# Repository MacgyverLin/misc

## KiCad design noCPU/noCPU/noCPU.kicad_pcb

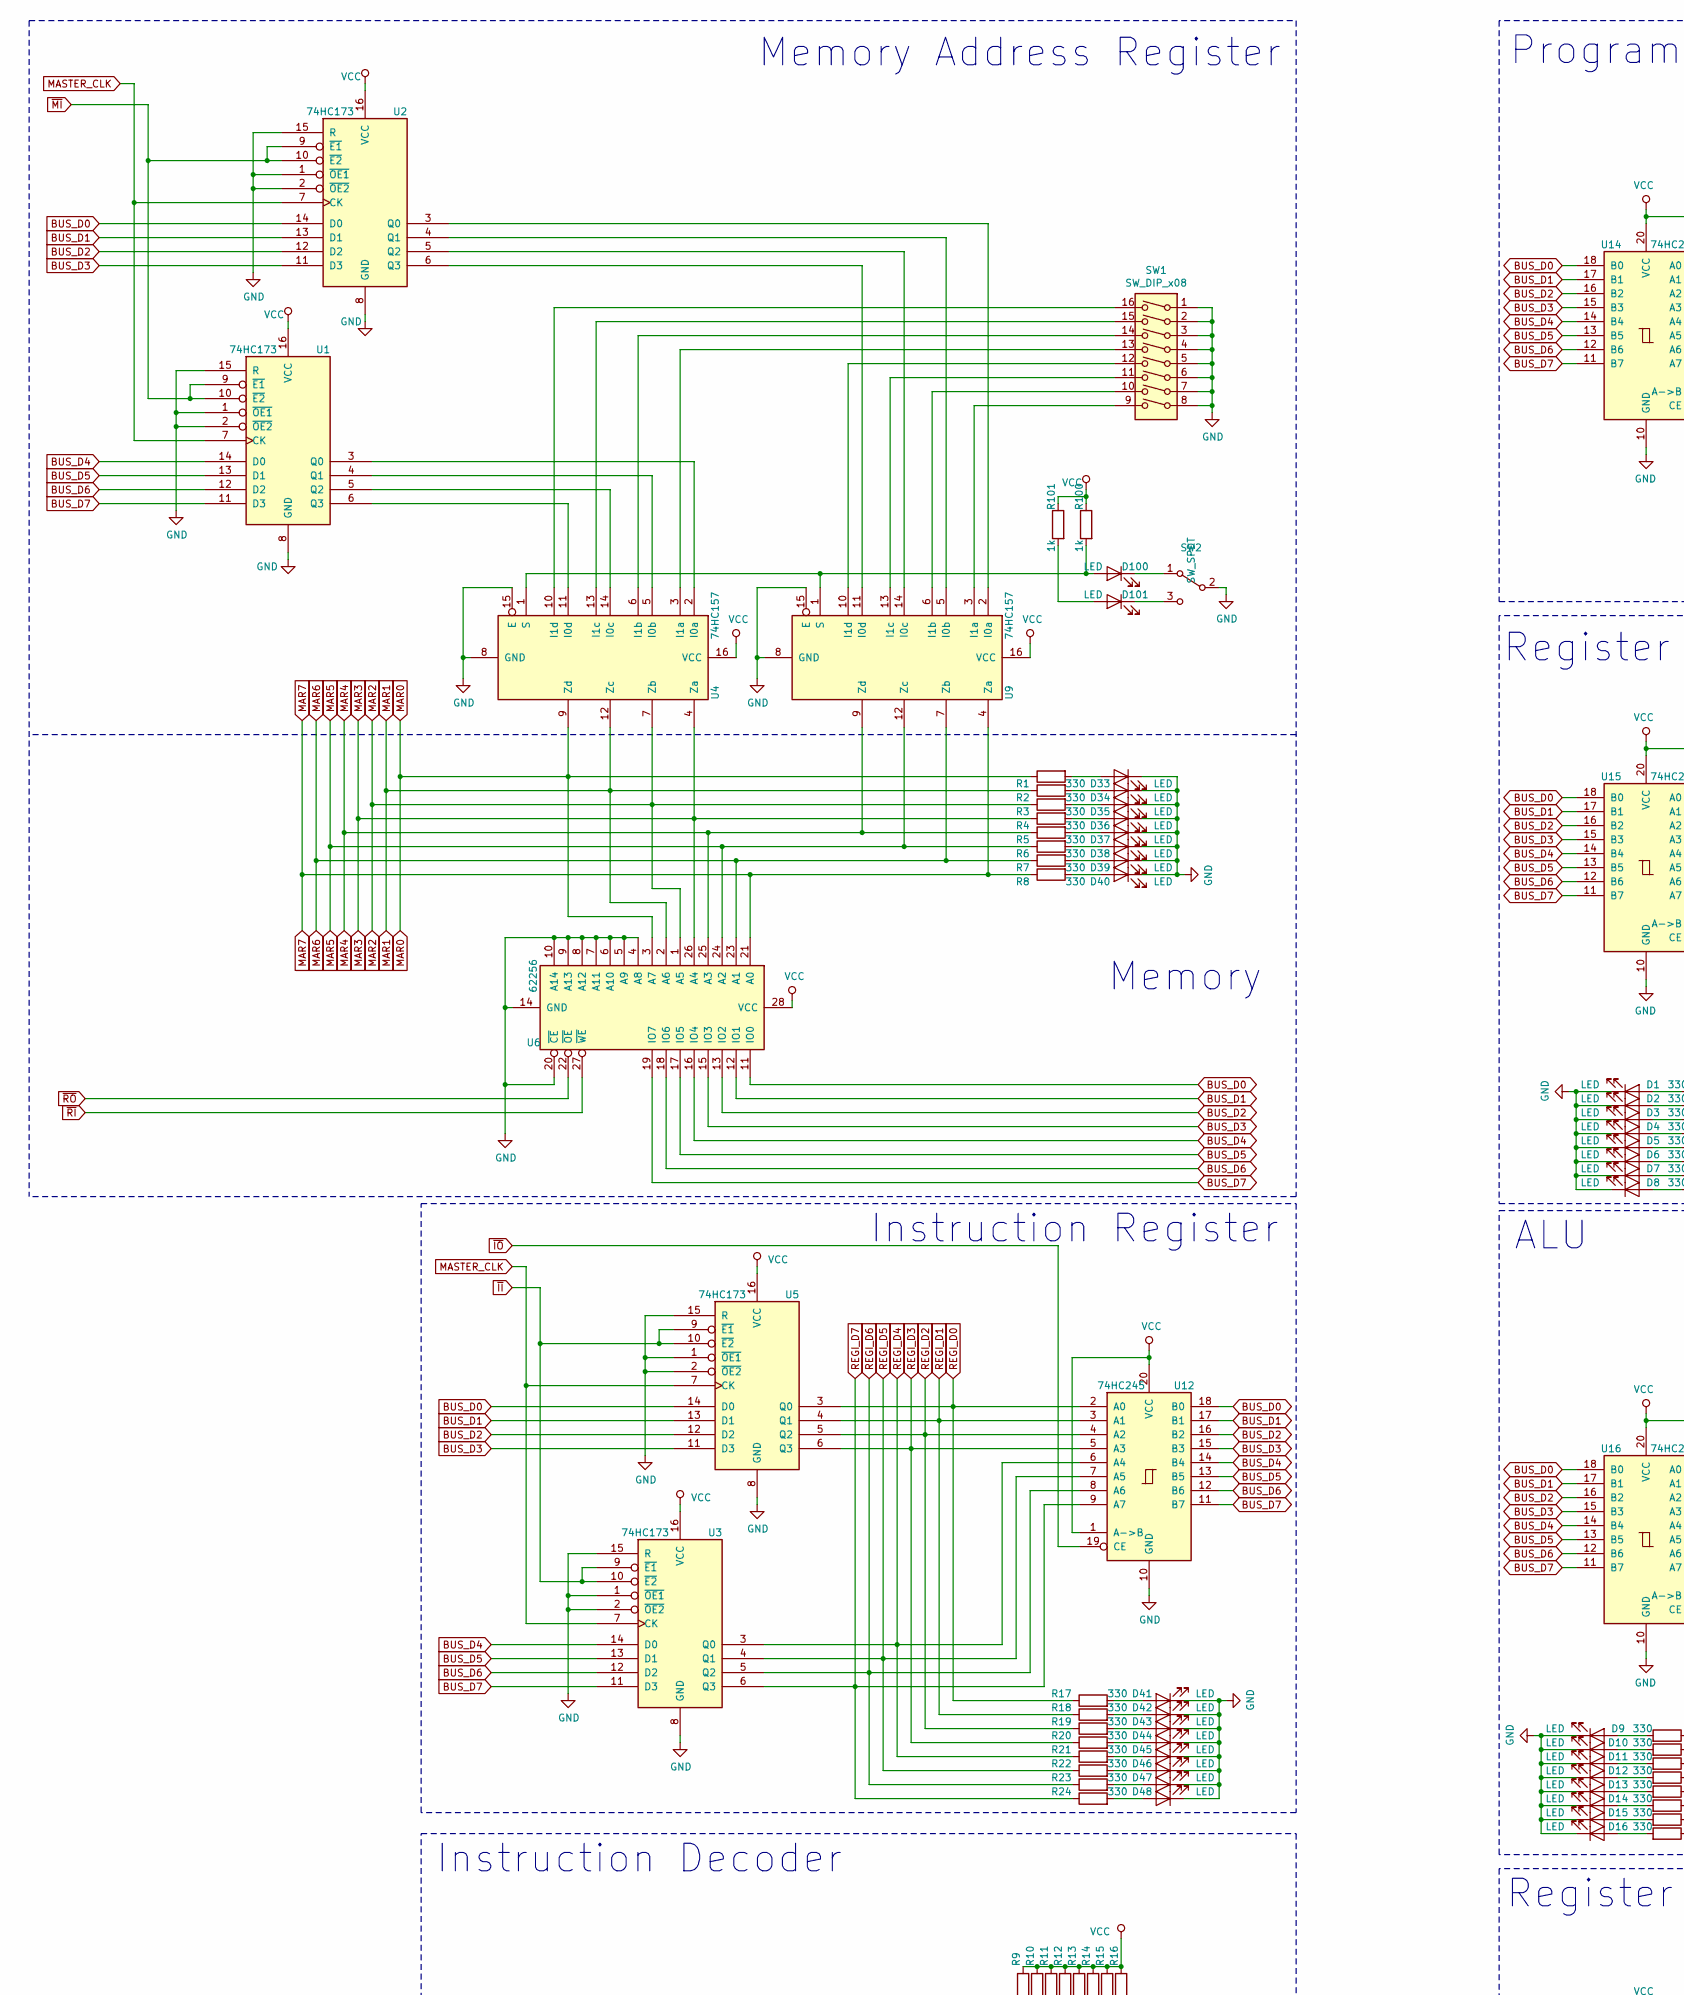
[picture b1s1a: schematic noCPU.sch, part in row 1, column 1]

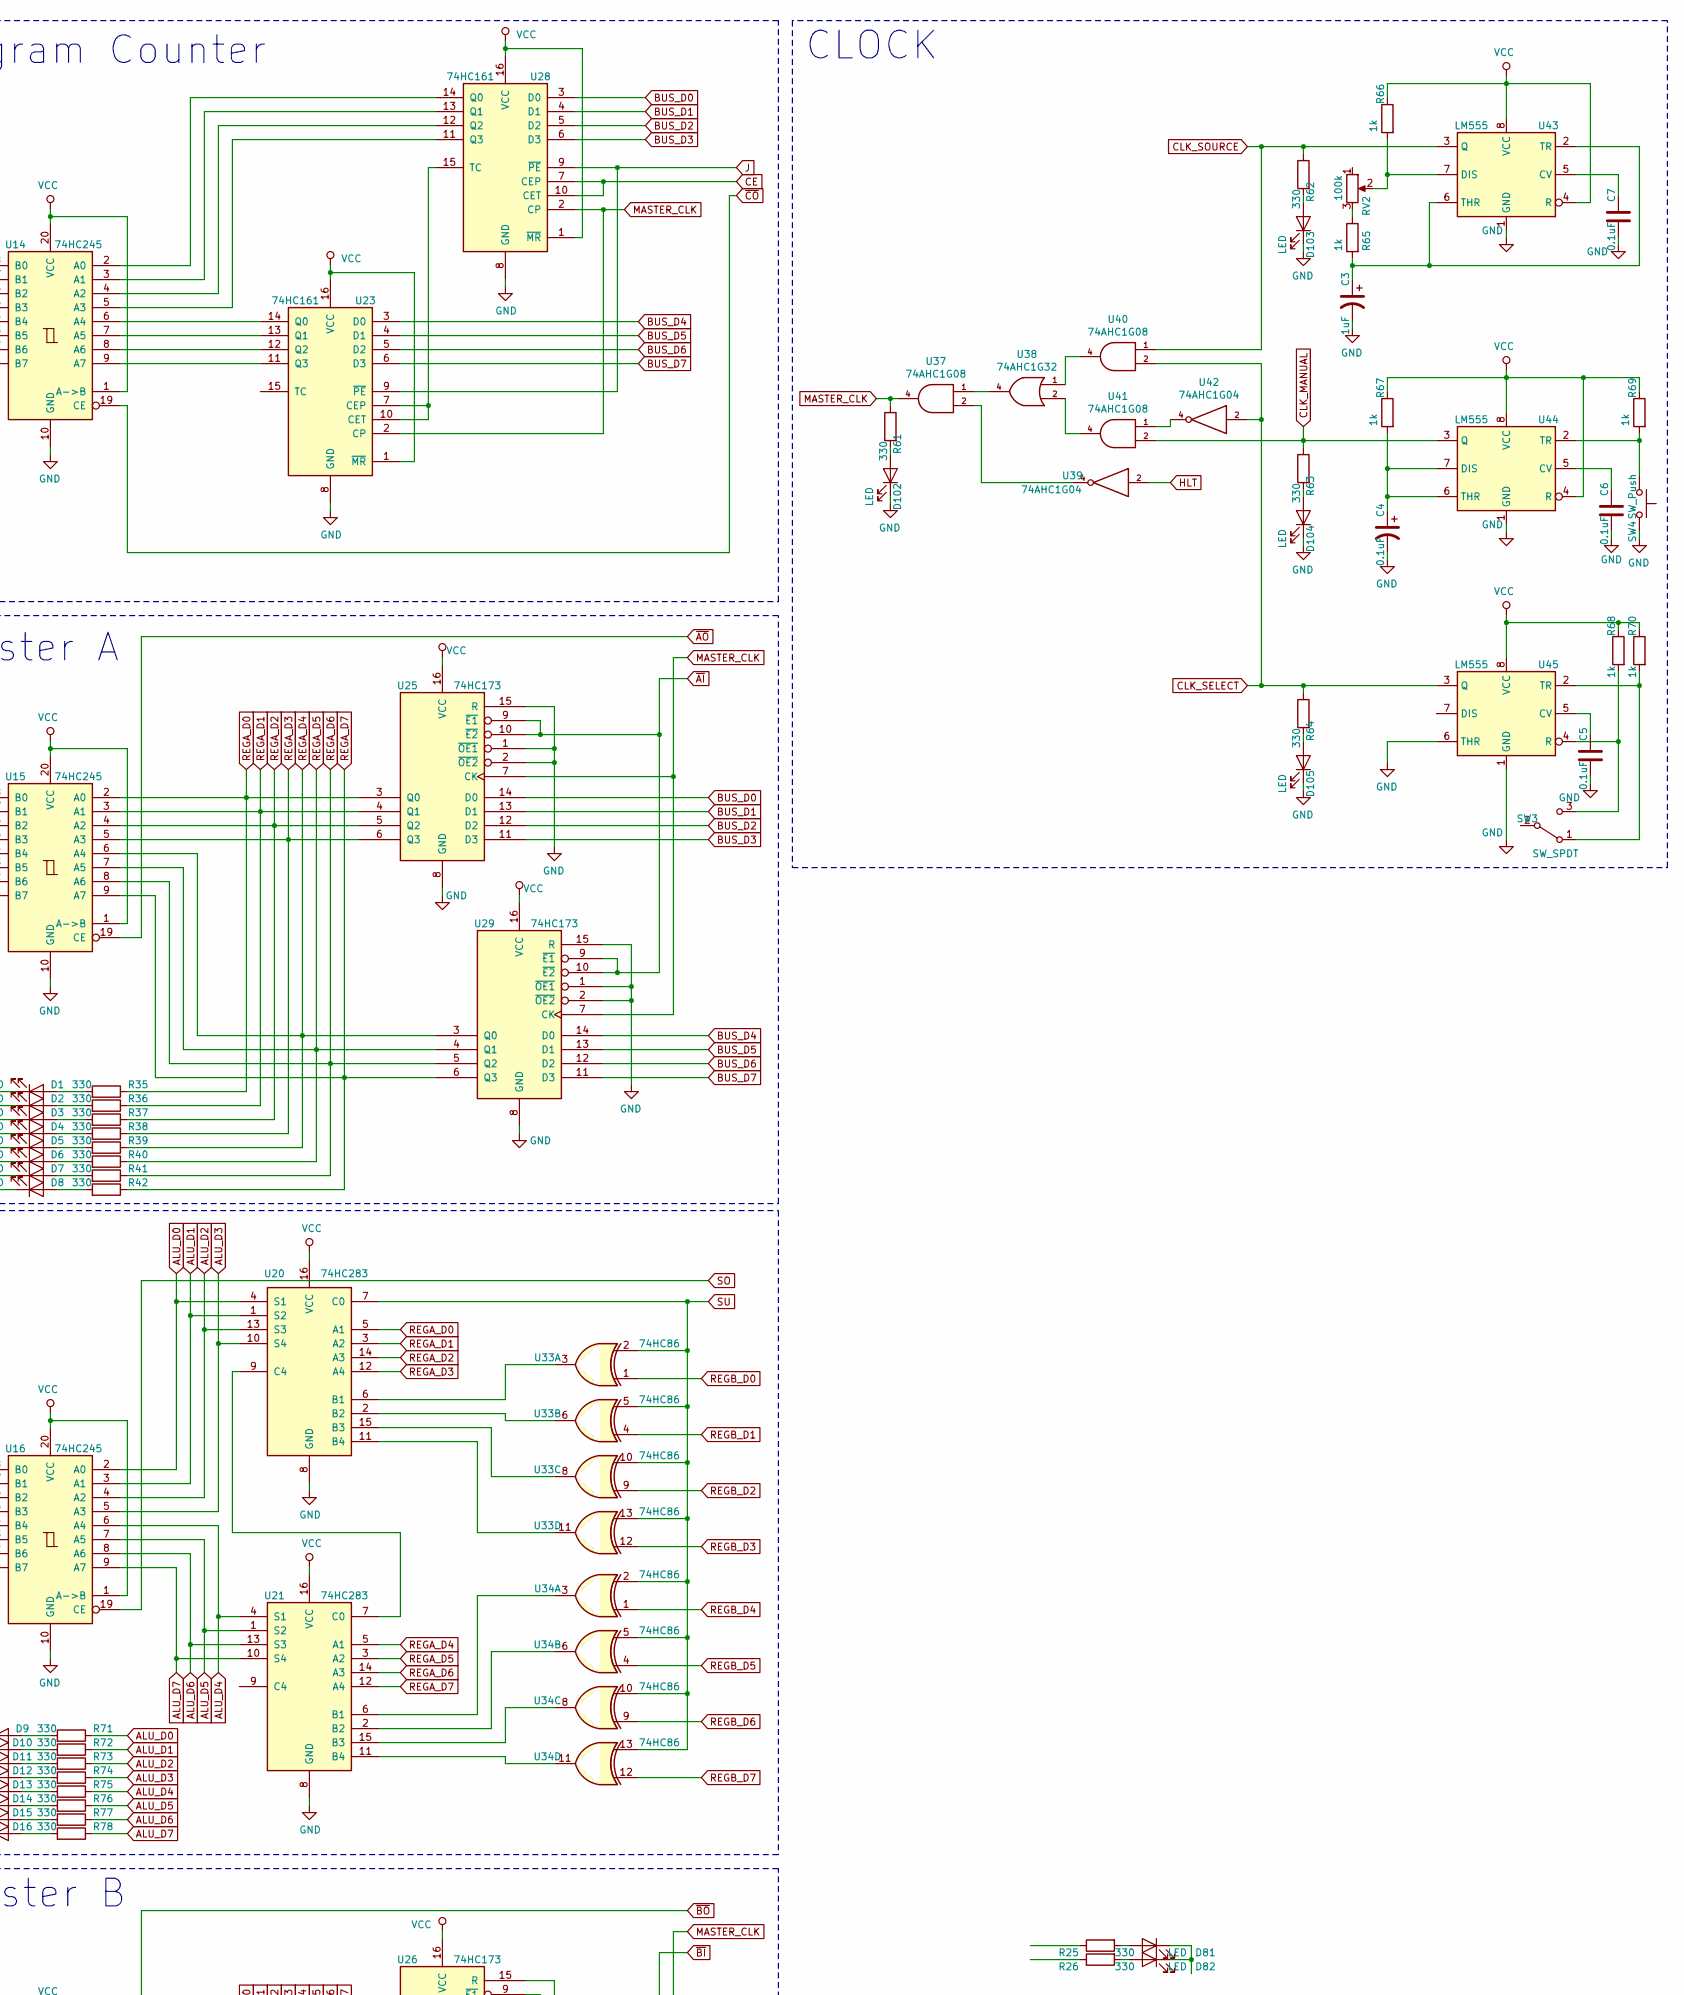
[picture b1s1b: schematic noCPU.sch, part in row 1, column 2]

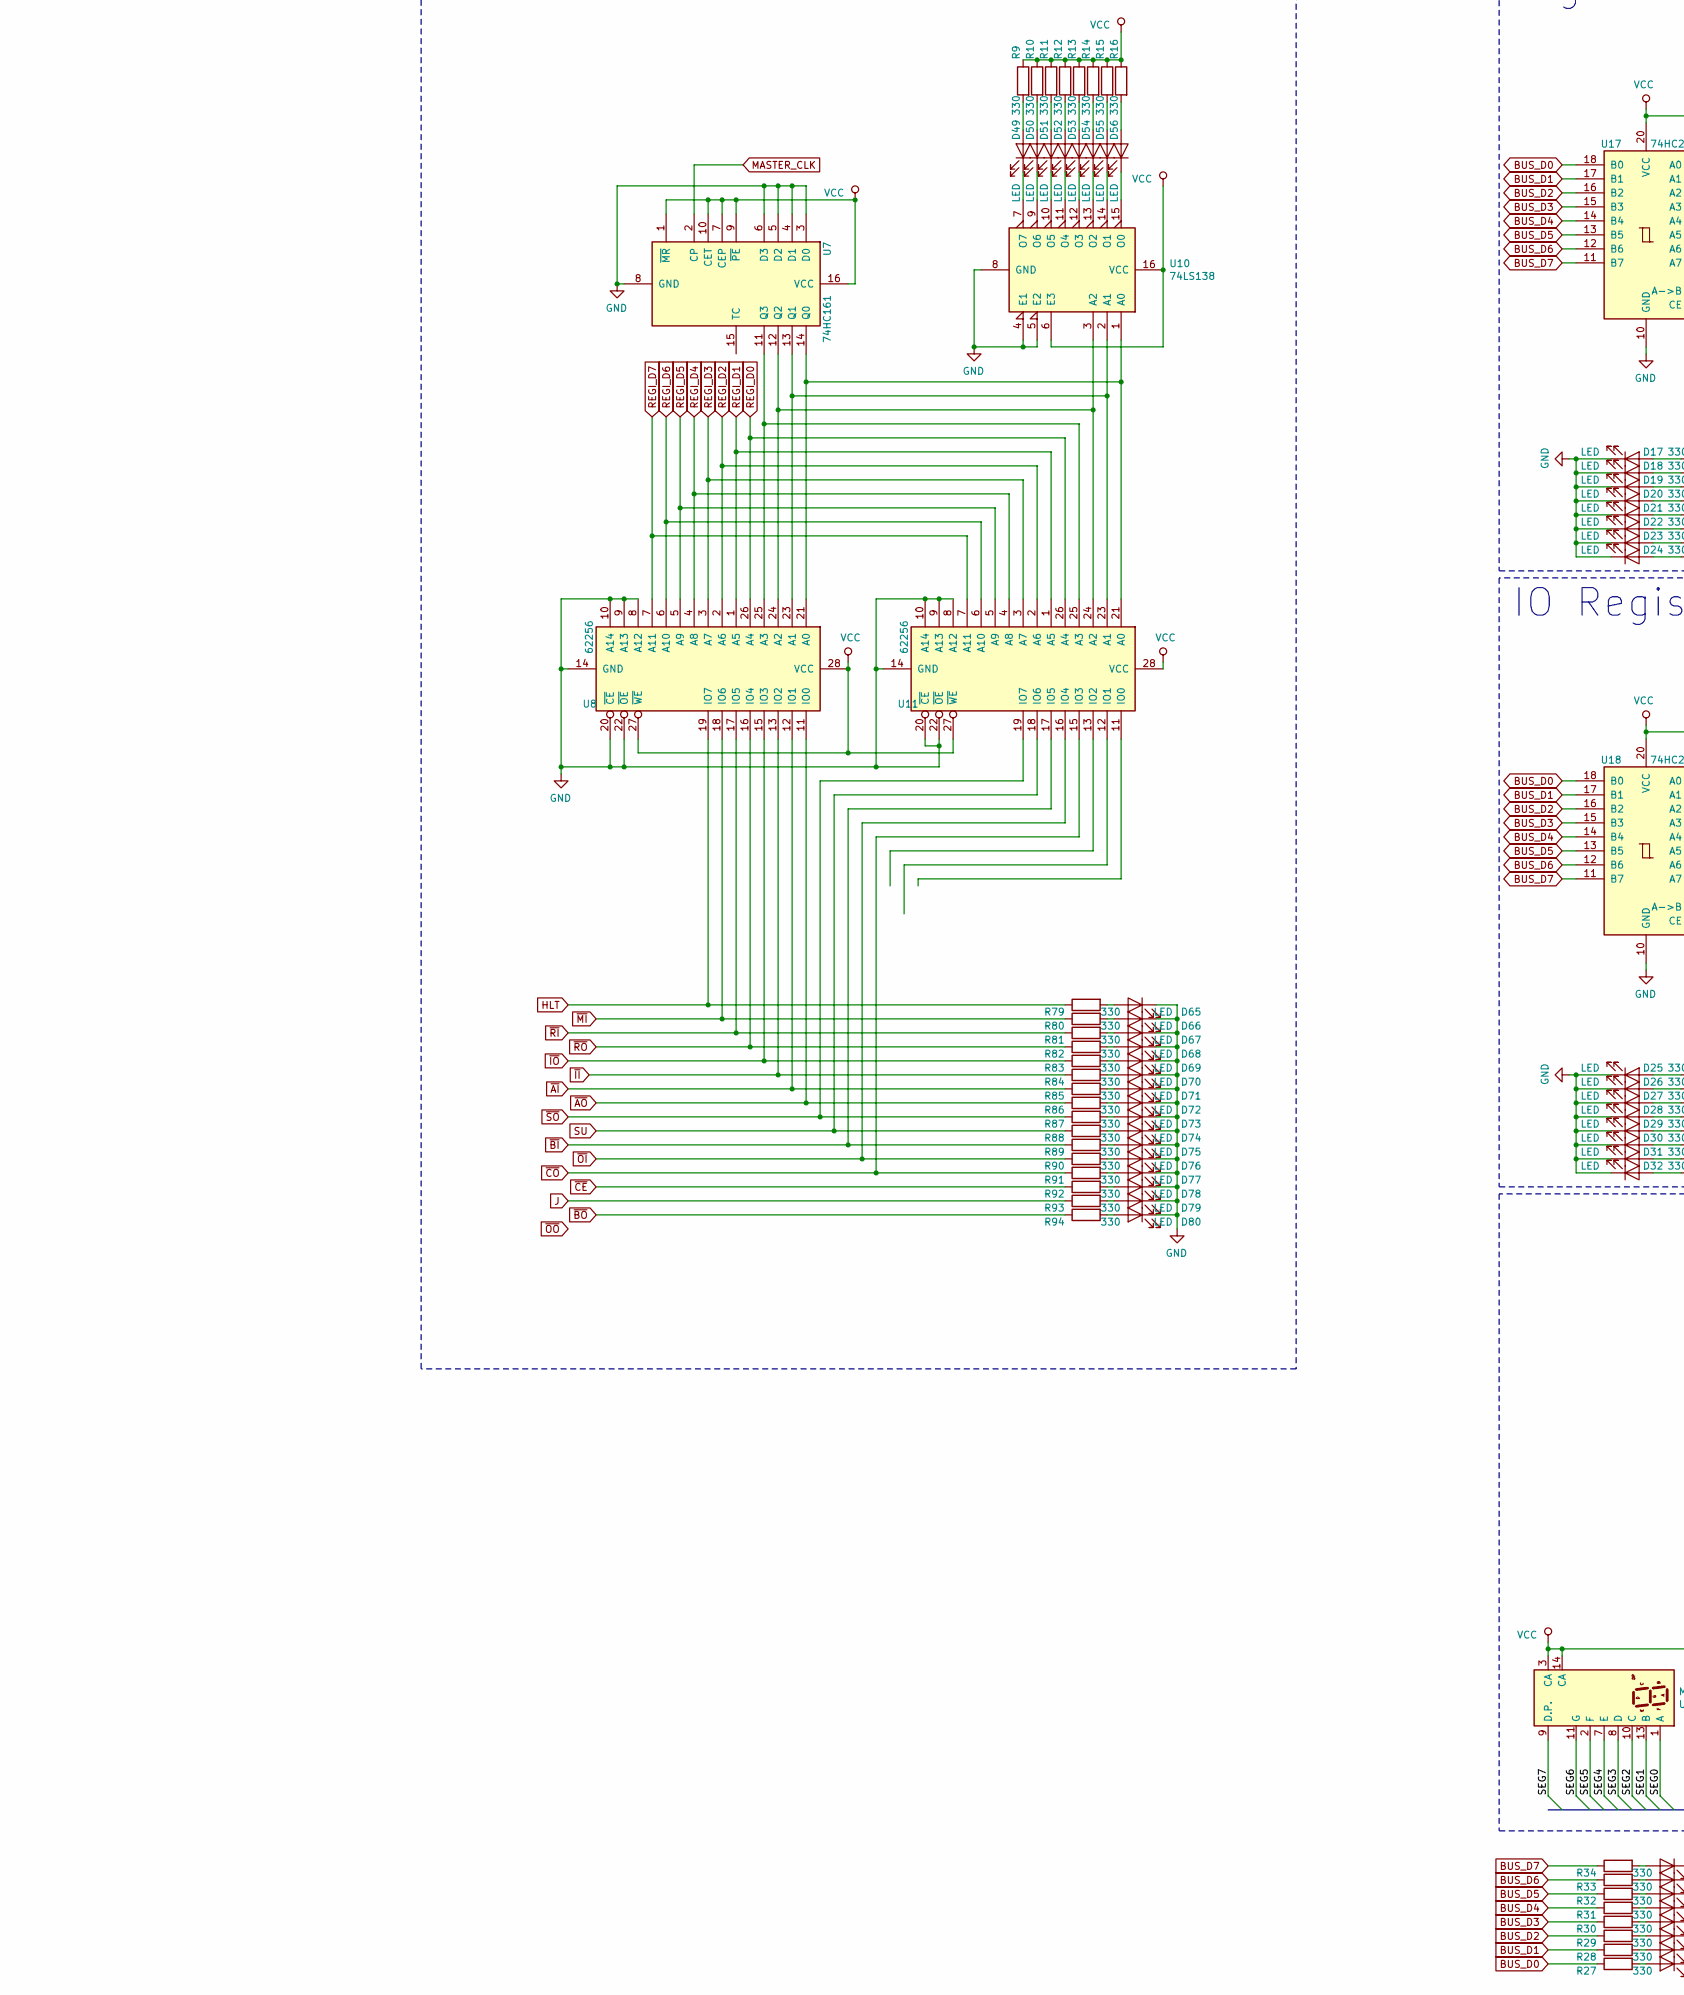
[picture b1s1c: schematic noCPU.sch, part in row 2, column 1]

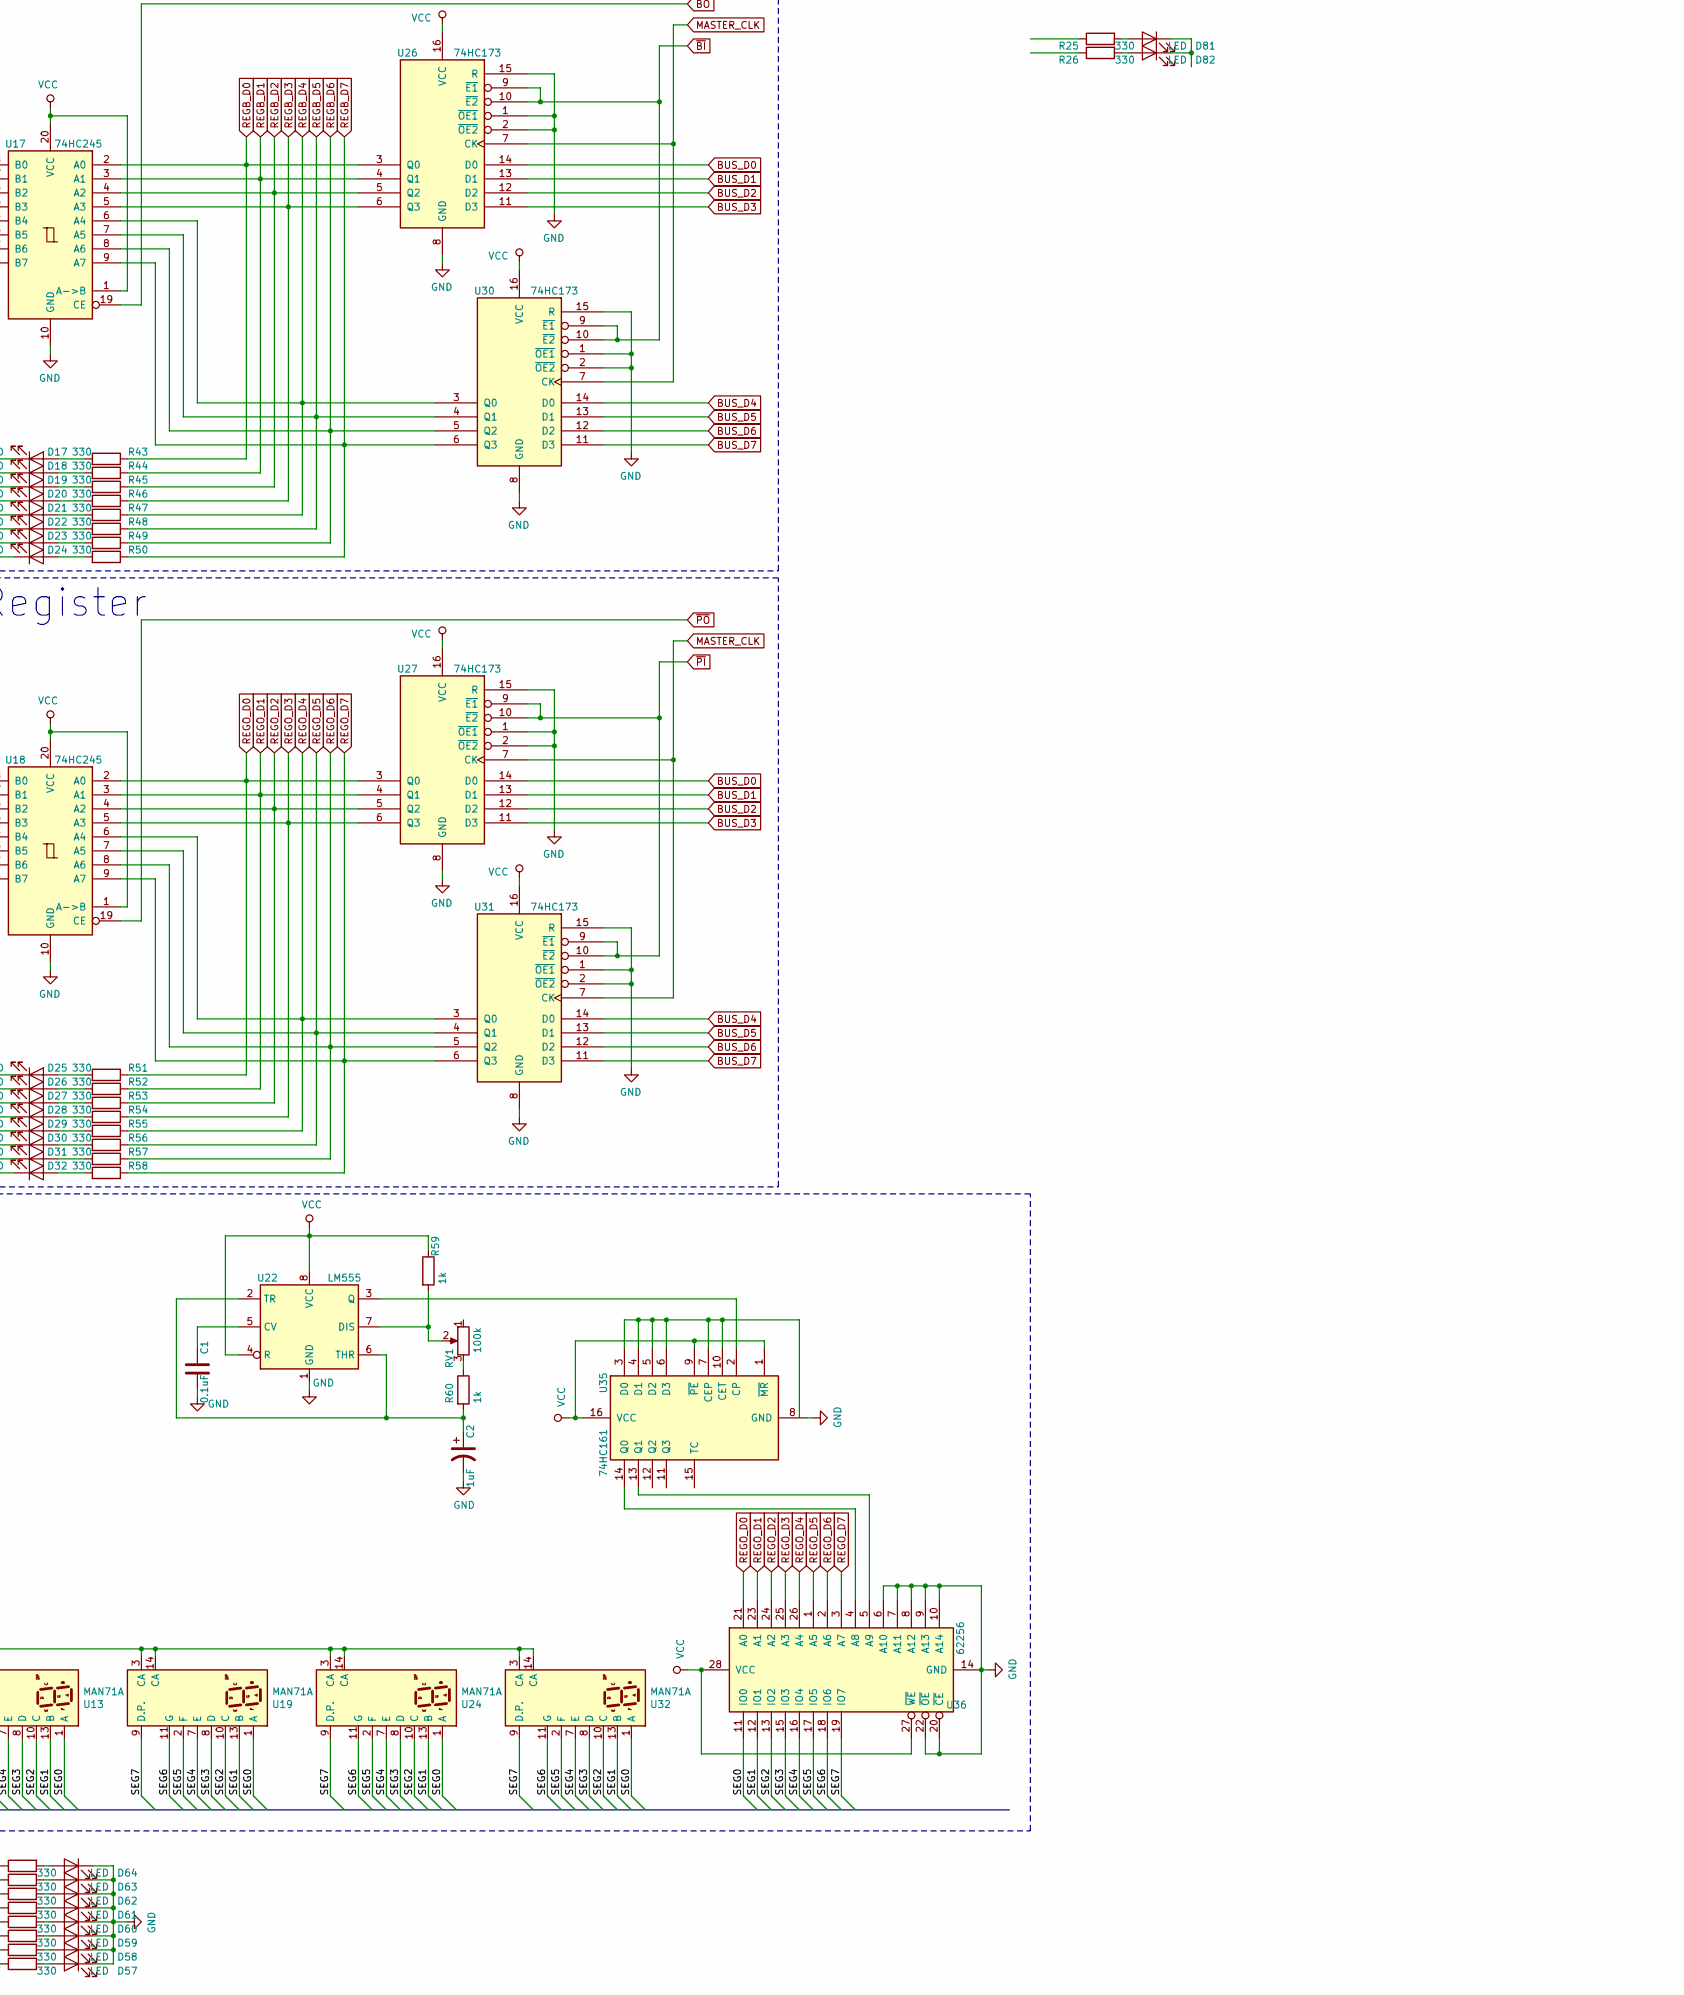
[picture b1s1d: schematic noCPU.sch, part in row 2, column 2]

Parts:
C1, C5, C6, C7: 0.1uF; C_0805_2012Metric
C2, C3: 1uF; CP_Radial_D8.0mm_P3.50mm
C4: 0.1uF; CP_Radial_D8.0mm_P3.50mm
D1, D2, D3, D4, D5, D6, D7, D8, D9, D10, D11, D12, D13, D14, D15, D16, D17, D18, D19, D20, D21, D22, D23, D24, D25, D26, D27, D28, D29, D30, D31, D32, D33, D34, D35, D36, D37, D38, D39, D40, D41, D42, D43, D44, D45, D46, D47, D48, D49, D50, D51, D52, D53, D54, D55, D56, D57, D58, D59, D60, D61, D62, D63, D64, D65, D66, D67, D68, D69, D70, D71, D72, D73, D74, D75, D76, D77, D78, D79, D80, D81, D82, D100, D101, D102, D103, D104, D105: LED; LED_0805_2012Metric
R1, R2, R3, R4, R5, R6, R7, R8, R9, R10, R11, R12, R13, R14, R15, R16, R17, R18, R19, R20, R21, R22, R23, R24, R25, R26, R27, R28, R29, R30, R31, R32, R33, R34, R35, R36, R37, R38, R39, R40, R41, R42, R43, R44, R45, R46, R47, R48, R49, R50, R51, R52, R53, R54, R55, R56, R57, R58, R61, R62, R63, R64, R71, R72, R73, R74, R75, R76, R77, R78, R79, R80, R81, R82, R83, R84, R85, R86, R87, R88, R89, R90, R91, R92, R93, R94: 330; R_0805_2012Metric
R59, R60, R65, R66, R67, R68, R69, R70, R100, R101: 1k; R_0805_2012Metric
RV1: 100k; PinHeader_1x03_P2.54mm_Vertical
RV2: 100k; PinHeader_1x03_P2.54mm_Horizontal
SW1: SW_DIP_x08; DIP-16_W7.62mm
SW2, SW3: SW_SPDT; PinSocket_1x03_P2.54mm_Vertical
SW4: SW_Push; DIP-4_W7.62mm
U1, U2, U3, U5, U25, U26, U27, U29, U30, U31: 74HC173; DIP-16_W7.62mm
U4, U9: 74HC157; DIP-16_W7.62mm
U6, U8, U11, U36: 62256; DIP-28_W15.24mm
U7, U23, U28, U35: 74HC161; DIP-16_W7.62mm
U10: 74LS138; DIP-18_W7.62mm
U12, U14, U15, U16, U17, U18: 74HC245; DIP-20_W7.62mm
U13, U19, U24, U32: MAN71A
U20, U21: 74HC283; DIP-16_W7.62mm
U22, U43, U44, U45: LM555; DIP-8_W7.62mm
U33, U34: 74HC86; DIP-14_W7.62mm
U37, U40, U41: 74AHC1G08; DIP-14_W7.62mm
U38: 74AHC1G32; DIP-14_W7.62mm
U39, U42: 74AHC1G04; DIP-14_W7.62mm

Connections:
/SEG0: U13.1 (A), U19.1 (A), U24.1 (A), U32.1 (A), U36.11 (IO0)
/SEG1: U13.13 (B), U19.13 (B), U24.13 (B), U32.13 (B), U36.12 (IO1)
/SEG2: U13.10 (C), U19.10 (C), U24.10 (C), U32.10 (C), U36.13 (IO2)
/SEG3: U13.8 (D), U19.8 (D), U24.8 (D), U32.8 (D), U36.15 (IO3)
/SEG4: U13.7 (E), U19.7 (E), U24.7 (E), U32.7 (E), U36.16 (IO4)
/SEG5: U13.2 (F), U19.2 (F), U24.2 (F), U32.2 (F), U36.17 (IO5)
/SEG6: U13.11 (G), U19.11 (G), U24.11 (G), U32.11 (G), U36.18 (IO6)
/SEG7: U13.9 (D.P.), U19.9 (D.P.), U24.9 (D.P.), U32.9 (D.P.), U36.19 (IO7)
ALU_D0: R71.1, U16.2 (A0), U20.4 (S1)
ALU_D1: R72.1, U16.3 (A1), U20.1 (S2)
ALU_D2: R73.1, U16.4 (A2), U20.13 (S3)
ALU_D3: R74.1, U16.5 (A3), U20.10 (S4)
ALU_D4: R75.1, U16.6 (A4), U21.4 (S1)
ALU_D5: R76.1, U16.7 (A5), U21.1 (S2)
ALU_D6: R77.1, U16.8 (A6), U21.13 (S3)
ALU_D7: R78.1, U16.9 (A7), U21.10 (S4)
BUS_D0: R27.1, U2.14 (D0), U5.14 (D0), U6.11 (IO0), U12.18 (B0), U14.18 (B0), U15.18 (B0), U16.18 (B0), U17.18 (B0), U18.18 (B0), U25.14 (D0), U26.14 (D0), U27.14 (D0), U28.3 (D0)
BUS_D1: R28.1, U2.13 (D1), U5.13 (D1), U6.12 (IO1), U12.17 (B1), U14.17 (B1), U15.17 (B1), U16.17 (B1), U17.17 (B1), U18.17 (B1), U25.13 (D1), U26.13 (D1), U27.13 (D1), U28.4 (D1)
BUS_D2: R29.1, U2.12 (D2), U5.12 (D2), U6.13 (IO2), U12.16 (B2), U14.16 (B2), U15.16 (B2), U16.16 (B2), U17.16 (B2), U18.16 (B2), U25.12 (D2), U26.12 (D2), U27.12 (D2), U28.5 (D2)
BUS_D3: R30.1, U2.11 (D3), U5.11 (D3), U6.15 (IO3), U12.15 (B3), U14.15 (B3), U15.15 (B3), U16.15 (B3), U17.15 (B3), U18.15 (B3), U25.11 (D3), U26.11 (D3), U27.11 (D3), U28.6 (D3)
BUS_D4: R31.1, U1.14 (D0), U3.14 (D0), U6.16 (IO4), U12.14 (B4), U14.14 (B4), U15.14 (B4), U16.14 (B4), U17.14 (B4), U18.14 (B4), U23.3 (D0), U29.14 (D0), U30.14 (D0), U31.14 (D0)
BUS_D5: R32.1, U1.13 (D1), U3.13 (D1), U6.17 (IO5), U12.13 (B5), U14.13 (B5), U15.13 (B5), U16.13 (B5), U17.13 (B5), U18.13 (B5), U23.4 (D1), U29.13 (D1), U30.13 (D1), U31.13 (D1)
BUS_D6: R33.1, U1.12 (D2), U3.12 (D2), U6.18 (IO6), U12.12 (B6), U14.12 (B6), U15.12 (B6), U16.12 (B6), U17.12 (B6), U18.12 (B6), U23.5 (D2), U29.12 (D2), U30.12 (D2), U31.12 (D2)
BUS_D7: R34.1, U1.11 (D3), U3.11 (D3), U6.19 (IO7), U12.11 (B7), U14.11 (B7), U15.11 (B7), U16.11 (B7), U17.11 (B7), U18.11 (B7), U23.6 (D3), U29.11 (D3), U30.11 (D3), U31.11 (D3)
CE: U28.7 (CEP), U28.10 (CET)
CLK_MANUAL: R63.1, U41.2, U44.3 (Q)
CLK_SELECT: R64.1, U40.2, U42.2, U45.3 (Q)
CLK_SOURCE: R62.1, U40.1, U43.3 (Q)
GND: C1.2, C2.2, C3.2, C4.2, C5.2, C6.2, C7.2, D1.1 (K), D2.1 (K), D3.1 (K), D4.1 (K), D5.1 (K), D6.1 (K), D7.1 (K), D8.1 (K), D9.1 (K), D10.1 (K), D11.1 (K), D12.1 (K), D13.1 (K), D14.1 (K), D15.1 (K), D16.1 (K), D17.1 (K), D18.1 (K), D19.1 (K), D20.1 (K), D21.1 (K), D22.1 (K), D23.1 (K), D24.1 (K), D25.1 (K), D26.1 (K), D27.1 (K), D28.1 (K), D29.1 (K), D30.1 (K), D31.1 (K), D32.1 (K), D33.1 (K), D34.1 (K), D35.1 (K), D36.1 (K), D37.1 (K), D38.1 (K), D39.1 (K), D40.1 (K), D41.1 (K), D42.1 (K), D43.1 (K), D44.1 (K), D45.1 (K), D46.1 (K), D47.1 (K), D48.1 (K), D57.1 (K), D58.1 (K), D59.1 (K), D60.1 (K), D61.1 (K), D62.1 (K), D63.1 (K), D64.1 (K), D65.1 (K), D66.1 (K), D67.1 (K), D68.1 (K), D69.1 (K), D70.1 (K), D71.1 (K), D72.1 (K), D73.1 (K), D74.1 (K), D75.1 (K), D76.1 (K), D77.1 (K), D78.1 (K), D79.1 (K), D80.1 (K), D102.1 (K), D103.1 (K), D104.1 (K), D105.1 (K), SW1.1, SW1.2, SW1.3, SW1.4, SW1.5, SW1.6, SW1.7, SW1.8, SW2.2 (B), SW4.1, U1.1 (~OE1), U1.2 (~OE2), U1.8 (GND), U1.15 (R), U2.1 (~OE1), U2.2 (~OE2), U2.8 (GND), U2.15 (R), U3.1 (~OE1), U3.2 (~OE2), U3.8 (GND), U3.15 (R), U4.8 (GND), U4.15 (E), U5.1 (~OE1), U5.2 (~OE2), U5.8 (GND), U5.15 (R), U6.4 (A8), U6.5 (A9), U6.6 (A10), U6.7 (A11), U6.8 (A12), U6.9 (A13), U6.10 (A14), U6.14 (GND), U6.20 (~CE), U7.3 (D0), U7.4 (D1), U7.5 (D2), U7.6 (D3), U7.8 (GND), U8.8 (A12), U8.9 (A13), U8.10 (A14), U8.14 (GND), U8.20 (~CE), U8.22 (~OE), U9.8 (GND), U9.15 (E), U10.4 (E1), U10.5 (E2), U10.8 (GND), U11.8 (A12), U11.9 (A13), U11.10 (A14), U11.14 (GND), U11.20 (~CE), U11.22 (~OE), U12.10 (GND), U14.10 (GND), U15.10 (GND), U16.10 (GND), U17.10 (GND), U18.10 (GND), U20.8 (GND), U21.8 (GND), U22.1 (GND), U23.8 (GND), U25.1 (~OE1), U25.2 (~OE2), U25.8 (GND), U25.15 (R), U26.1 (~OE1), U26.2 (~OE2), U26.8 (GND), U26.15 (R), U27.1 (~OE1), U27.2 (~OE2), U27.8 (GND), U27.15 (R), U28.8 (GND), U29.1 (~OE1), U29.2 (~OE2), U29.8 (GND), U29.15 (R), U30.1 (~OE1), U30.2 (~OE2), U30.8 (GND), U30.15 (R), U31.1 (~OE1), U31.2 (~OE2), U31.8 (GND), U31.15 (R), U35.8 (GND), U36.6 (A10), U36.7 (A11), U36.8 (A12), U36.9 (A13), U36.10 (A14), U36.14 (GND), U36.20 (~CE), U36.22 (~OE), U37.3 (GND), U38.3 (GND), U39.3 (GND), U40.3 (GND), U41.3 (GND), U42.3 (GND), U43.1 (GND), U44.1 (GND), U45.1 (GND), U45.6 (THR)
HLT: R79.1, U8.19 (IO7), U39.2
J: R93.1, U23.9 (~PE), U28.9 (~PE)
MAR0: R1.1, U4.9 (Zd), U6.3 (A7)
MAR1: R2.1, U4.12 (Zc), U6.2 (A6)
MAR2: R3.1, U4.7 (Zb), U6.1 (A5)
MAR3: R4.1, U4.4 (Za), U6.26 (A4)
MAR4: R5.1, U6.25 (A3), U9.9 (Zd)
MAR5: R6.1, U6.24 (A2), U9.12 (Zc)
MAR6: R7.1, U6.23 (A1), U9.7 (Zb)
MAR7: R8.1, U6.21 (A0), U9.4 (Za)
MASTER_CLK: R61.1, U1.7 (CK), U2.7 (CK), U3.7 (CK), U5.7 (CK), U7.2 (CP), U23.2 (CP), U25.7 (CK), U26.7 (CK), U27.7 (CK), U28.2 (CP), U29.7 (CK), U30.7 (CK), U31.7 (CK), U37.4
unnamed: C1.1, U22.5 (CV)
unnamed: C2.1, R60.2, U22.2 (TR), U22.6 (THR)
unnamed: C3.1, R65.2, U43.2 (TR), U43.6 (THR)
unnamed: C4.1, R67.2, U44.6 (THR), U44.7 (DIS)
unnamed: C5.1, U45.5 (CV)
unnamed: C6.1, U44.5 (CV)
unnamed: C7.1, U43.5 (CV)
unnamed: D1.2 (A), R35.2
unnamed: D2.2 (A), R36.2
unnamed: D3.2 (A), R37.2
unnamed: D4.2 (A), R38.2
unnamed: D5.2 (A), R39.2
unnamed: D6.2 (A), R40.2
unnamed: D7.2 (A), R41.2
unnamed: D8.2 (A), R42.2
unnamed: D9.2 (A), R71.2
unnamed: D10.2 (A), R72.2
unnamed: D11.2 (A), R73.2
unnamed: D12.2 (A), R74.2
unnamed: D13.2 (A), R75.2
unnamed: D14.2 (A), R76.2
unnamed: D15.2 (A), R77.2
unnamed: D16.2 (A), R78.2
unnamed: D17.2 (A), R43.2
unnamed: D18.2 (A), R44.2
unnamed: D19.2 (A), R45.2
unnamed: D20.2 (A), R46.2
unnamed: D21.2 (A), R47.2
unnamed: D22.2 (A), R48.2
unnamed: D23.2 (A), R49.2
unnamed: D24.2 (A), R50.2
unnamed: D25.2 (A), R51.2
unnamed: D26.2 (A), R52.2
unnamed: D27.2 (A), R53.2
unnamed: D28.2 (A), R54.2
unnamed: D29.2 (A), R55.2
unnamed: D30.2 (A), R56.2
unnamed: D31.2 (A), R57.2
unnamed: D32.2 (A), R58.2
unnamed: D33.2 (A), R1.2
unnamed: D34.2 (A), R2.2
unnamed: D35.2 (A), R3.2
unnamed: D36.2 (A), R4.2
unnamed: D37.2 (A), R5.2
unnamed: D38.2 (A), R6.2
unnamed: D39.2 (A), R7.2
unnamed: D40.2 (A), R8.2
unnamed: D41.2 (A), R17.2
unnamed: D42.2 (A), R18.2
unnamed: D43.2 (A), R19.2
unnamed: D44.2 (A), R20.2
unnamed: D45.2 (A), R21.2
unnamed: D46.2 (A), R22.2
unnamed: D47.2 (A), R23.2
unnamed: D48.2 (A), R24.2
unnamed: D49.1 (K), U10.7 (O7)
unnamed: D49.2 (A), R9.2
unnamed: D50.1 (K), U10.9 (O6)
unnamed: D50.2 (A), R10.2
unnamed: D51.1 (K), U10.10 (O5)
unnamed: D51.2 (A), R11.2
unnamed: D52.1 (K), U10.11 (O4)
unnamed: D52.2 (A), R12.2
unnamed: D53.1 (K), U10.12 (O3)
unnamed: D53.2 (A), R13.2
unnamed: D54.1 (K), U10.13 (O2)
unnamed: D54.2 (A), R14.2
unnamed: D55.1 (K), U10.14 (O1)
unnamed: D55.2 (A), R15.2
unnamed: D56.1 (K), U10.15 (O0)
unnamed: D56.2 (A), R16.2
unnamed: D57.2 (A), R27.2
unnamed: D58.2 (A), R28.2
unnamed: D59.2 (A), R29.2
unnamed: D60.2 (A), R30.2
unnamed: D61.2 (A), R31.2
unnamed: D62.2 (A), R32.2
unnamed: D63.2 (A), R33.2
unnamed: D64.2 (A), R34.2
unnamed: D65.2 (A), R79.2
unnamed: D66.2 (A), R80.2
unnamed: D67.2 (A), R81.2
unnamed: D68.2 (A), R82.2
unnamed: D69.2 (A), R83.2
unnamed: D70.2 (A), R84.2
unnamed: D71.2 (A), R85.2
unnamed: D72.2 (A), R86.2
unnamed: D73.2 (A), R87.2
unnamed: D74.2 (A), R88.2
unnamed: D75.2 (A), R89.2
unnamed: D76.2 (A), R90.2
unnamed: D77.2 (A), R91.2
unnamed: D78.2 (A), R92.2
unnamed: D79.2 (A), R93.2
unnamed: D80.2 (A), R94.2
unnamed: D81.1 (K), D82.1 (K)
unnamed: D81.2 (A), R25.2
unnamed: D82.2 (A), R26.2
unnamed: D100.1 (K), SW2.1 (A)
unnamed: D100.2 (A), R100.2, U4.1 (S), U9.1 (S)
unnamed: D101.1 (K), SW2.3 (C)
unnamed: D101.2 (A), R101.2
unnamed: D102.2 (A), R61.2
unnamed: D103.2 (A), R62.2
unnamed: D104.2 (A), R63.2
unnamed: D105.2 (A), R64.2
unnamed: R59.2, RV1.2, U22.7 (DIS)
unnamed: R60.1, RV1.3
unnamed: R65.1, RV2.3
unnamed: R66.2, RV2.2, U43.7 (DIS)
unnamed: R68.2, SW3.3 (C), U45.4 (R)
unnamed: R69.2, SW4.2, U44.2 (TR)
unnamed: R70.2, SW3.1 (A), U45.2 (TR)
unnamed: SW1.9, U9.3 (I1a)
unnamed: SW1.10, U9.6 (I1b)
unnamed: SW1.11, U9.13 (I1c)
unnamed: SW1.12, U9.10 (I1d)
unnamed: SW1.13, U4.3 (I1a)
unnamed: SW1.14, U4.6 (I1b)
unnamed: SW1.15, U4.13 (I1c)
unnamed: SW1.16, U4.10 (I1d)
unnamed: U1.3 (Q0), U4.2 (I0a)
unnamed: U1.4 (Q1), U4.5 (I0b)
unnamed: U1.5 (Q2), U4.14 (I0c)
unnamed: U1.6 (Q3), U4.11 (I0d)
unnamed: U2.3 (Q0), U9.2 (I0a)
unnamed: U2.4 (Q1), U9.5 (I0b)
unnamed: U2.5 (Q2), U9.14 (I0c)
unnamed: U2.6 (Q3), U9.11 (I0d)
unnamed: U7.14 (Q0), U8.21 (A0), U10.1 (A0), U11.21 (A0)
unnamed: U7.13 (Q1), U8.23 (A1), U10.2 (A1), U11.23 (A1)
unnamed: U7.12 (Q2), U8.24 (A2), U10.3 (A2), U11.24 (A2)
unnamed: U7.11 (Q3), U8.25 (A3), U11.25 (A3)
unnamed: U14.2 (A0), U28.14 (Q0)
unnamed: U14.3 (A1), U28.13 (Q1)
unnamed: U14.4 (A2), U28.12 (Q2)
unnamed: U14.5 (A3), U28.11 (Q3)
unnamed: U14.6 (A4), U23.14 (Q0)
unnamed: U14.7 (A5), U23.13 (Q1)
unnamed: U14.8 (A6), U23.12 (Q2)
unnamed: U14.9 (A7), U23.11 (Q3)
unnamed: U20.2 (B2), U33.6
unnamed: U20.6 (B1), U33.3
unnamed: U20.9 (C4), U21.7 (C0)
unnamed: U20.11 (B4), U33.11
unnamed: U20.15 (B3), U33.8
unnamed: U21.2 (B2), U34.6
unnamed: U21.6 (B1), U34.3
unnamed: U21.11 (B4), U34.11
unnamed: U21.15 (B3), U34.8
unnamed: U22.3 (Q), U35.2 (CP)
unnamed: U23.7 (CEP), U23.10 (CET), U28.15 (TC)
unnamed: U35.3 (D0), U35.4 (D1), U35.5 (D2), U35.6 (D3), U35.7 (CEP), U35.10 (CET)
unnamed: U35.13 (Q1), U36.5 (A9)
unnamed: U35.14 (Q0), U36.4 (A8)
unnamed: U37.1, U38.4
unnamed: U37.2, U39.4
unnamed: U38.1, U40.4
unnamed: U38.2, U41.4
unnamed: U41.1, U42.4
REGA_D0: R35.1, U15.2 (A0), U20.5 (A1), U25.3 (Q0)
REGA_D1: R36.1, U15.3 (A1), U20.3 (A2), U25.4 (Q1)
REGA_D2: R37.1, U15.4 (A2), U20.14 (A3), U25.5 (Q2)
REGA_D3: R38.1, U15.5 (A3), U20.12 (A4), U25.6 (Q3)
REGA_D4: R39.1, U15.6 (A4), U21.5 (A1), U29.3 (Q0)
REGA_D5: R40.1, U15.7 (A5), U21.3 (A2), U29.4 (Q1)
REGA_D6: R41.1, U15.8 (A6), U21.14 (A3), U29.5 (Q2)
REGA_D7: R42.1, U15.9 (A7), U21.12 (A4), U29.6 (Q3)
REGB_D0: R43.1, U17.2 (A0), U26.3 (Q0), U33.1
REGB_D1: R44.1, U17.3 (A1), U26.4 (Q1), U33.4
REGB_D2: R45.1, U17.4 (A2), U26.5 (Q2), U33.9
REGB_D3: R46.1, U17.5 (A3), U26.6 (Q3), U33.12
REGB_D4: R47.1, U17.6 (A4), U30.3 (Q0), U34.1
REGB_D5: R48.1, U17.7 (A5), U30.4 (Q1), U34.4
REGB_D6: R49.1, U17.8 (A6), U30.5 (Q2), U34.9
REGB_D7: R50.1, U17.9 (A7), U30.6 (Q3), U34.12
REGI_D0: R17.1, U5.3 (Q0), U8.26 (A4), U11.26 (A4), U12.2 (A0)
REGI_D1: R18.1, U5.4 (Q1), U8.1 (A5), U11.1 (A5), U12.3 (A1)
REGI_D2: R19.1, U5.5 (Q2), U8.2 (A6), U11.2 (A6), U12.4 (A2)
REGI_D3: R20.1, U5.6 (Q3), U8.3 (A7), U11.3 (A7), U12.5 (A3)
REGI_D4: R21.1, U3.3 (Q0), U8.4 (A8), U11.4 (A8), U12.6 (A4)
REGI_D5: R22.1, U3.4 (Q1), U8.5 (A9), U11.5 (A9), U12.7 (A5)
REGI_D6: R23.1, U3.5 (Q2), U8.6 (A10), U11.6 (A10), U12.8 (A6)
REGI_D7: R24.1, U3.6 (Q3), U8.7 (A11), U11.7 (A11), U12.9 (A7)
REGO_D0: R51.1, U18.2 (A0), U27.3 (Q0), U36.21 (A0)
REGO_D1: R52.1, U18.3 (A1), U27.4 (Q1), U36.23 (A1)
REGO_D2: R53.1, U18.4 (A2), U27.5 (Q2), U36.24 (A2)
REGO_D3: R54.1, U18.5 (A3), U27.6 (Q3), U36.25 (A3)
REGO_D4: R55.1, U18.6 (A4), U31.3 (Q0), U36.26 (A4)
REGO_D5: R56.1, U18.7 (A5), U31.4 (Q1), U36.1 (A5)
REGO_D6: R57.1, U18.8 (A6), U31.5 (Q2), U36.2 (A6)
REGO_D7: R58.1, U18.9 (A7), U31.6 (Q3), U36.3 (A7)
SO: U16.19 (CE)
SU: R88.1, U11.18 (IO6), U20.7 (C0), U33.2, U33.5, U33.10, U33.13, U34.2, U34.5, U34.10, U34.13
VCC: R9.1, R10.1, R11.1, R12.1, R13.1, R14.1, R15.1, R16.1, R59.1, R66.1, R67.1, R68.1, R69.1, R70.1, R100.1, R101.1, U1.16 (VCC), U2.16 (VCC), U3.16 (VCC), U4.16 (VCC), U5.16 (VCC), U6.28 (VCC), U7.1 (~MR), U7.7 (CEP), U7.9 (~PE), U7.10 (CET), U7.16 (VCC), U8.27 (~WE), U8.28 (VCC), U9.16 (VCC), U10.6 (E3), U10.16 (VCC), U11.27 (~WE), U11.28 (VCC), U12.1 (A->B), U12.20 (VCC), U13.3 (CA), U13.14 (CA), U14.1 (A->B), U14.20 (VCC), U15.1 (A->B), U15.20 (VCC), U16.1 (A->B), U16.20 (VCC), U17.1 (A->B), U17.20 (VCC), U18.1 (A->B), U18.20 (VCC), U19.3 (CA), U19.14 (CA), U20.16 (VCC), U21.16 (VCC), U22.4 (R), U22.8 (VCC), U23.1 (~MR), U23.16 (VCC), U24.3 (CA), U24.14 (CA), U25.16 (VCC), U26.16 (VCC), U27.16 (VCC), U28.1 (~MR), U28.16 (VCC), U29.16 (VCC), U30.16 (VCC), U31.16 (VCC), U32.3 (CA), U32.14 (CA), U35.1 (~MR), U35.9 (~PE), U35.16 (VCC), U36.27 (~WE), U36.28 (VCC), U37.5 (VCC), U38.5 (VCC), U39.5 (VCC), U40.5 (VCC), U41.5 (VCC), U42.5 (VCC), U43.4 (R), U43.8 (VCC), U44.4 (R), U44.8 (VCC), U45.8 (VCC)
~AI: R85.1, U8.12 (IO1), U25.9 (~E1), U25.10 (~E2), U29.9 (~E1), U29.10 (~E2)
~AO: R86.1, U8.11 (IO0), U15.19 (CE)
~BI: R89.1, U11.17 (IO5), U26.9 (~E1), U26.10 (~E2), U30.9 (~E1), U30.10 (~E2)
~BO: R94.1, U17.19 (CE)
~CE: R92.1
~CO: R91.1, U11.15 (IO3), U14.19 (CE)
~II: R84.1, U3.9 (~E1), U3.10 (~E2), U5.9 (~E1), U5.10 (~E2), U8.13 (IO2)
~IO: R83.1, U8.15 (IO3), U12.19 (CE)
~MI: R80.1, U1.9 (~E1), U1.10 (~E2), U2.9 (~E1), U2.10 (~E2), U8.18 (IO6)
~OI: R90.1, U11.16 (IO4)
~PI: U27.9 (~E1), U27.10 (~E2), U31.9 (~E1), U31.10 (~E2)
~PO: U18.19 (CE)
~RI: R81.1, U6.27 (~WE), U8.17 (IO5)
~RO: R82.1, U6.22 (~OE), U8.16 (IO4)
~SO: R87.1, U11.19 (IO7)

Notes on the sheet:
Register A
ALU
CLOCK
Register B
Memory Address Register
Memory
Instruction Register
IO Register
Program Counter
Instruction Decoder

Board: 2 copper layers, 242 parts (0 on the bottom side), 247 nets, no tracks yet.
